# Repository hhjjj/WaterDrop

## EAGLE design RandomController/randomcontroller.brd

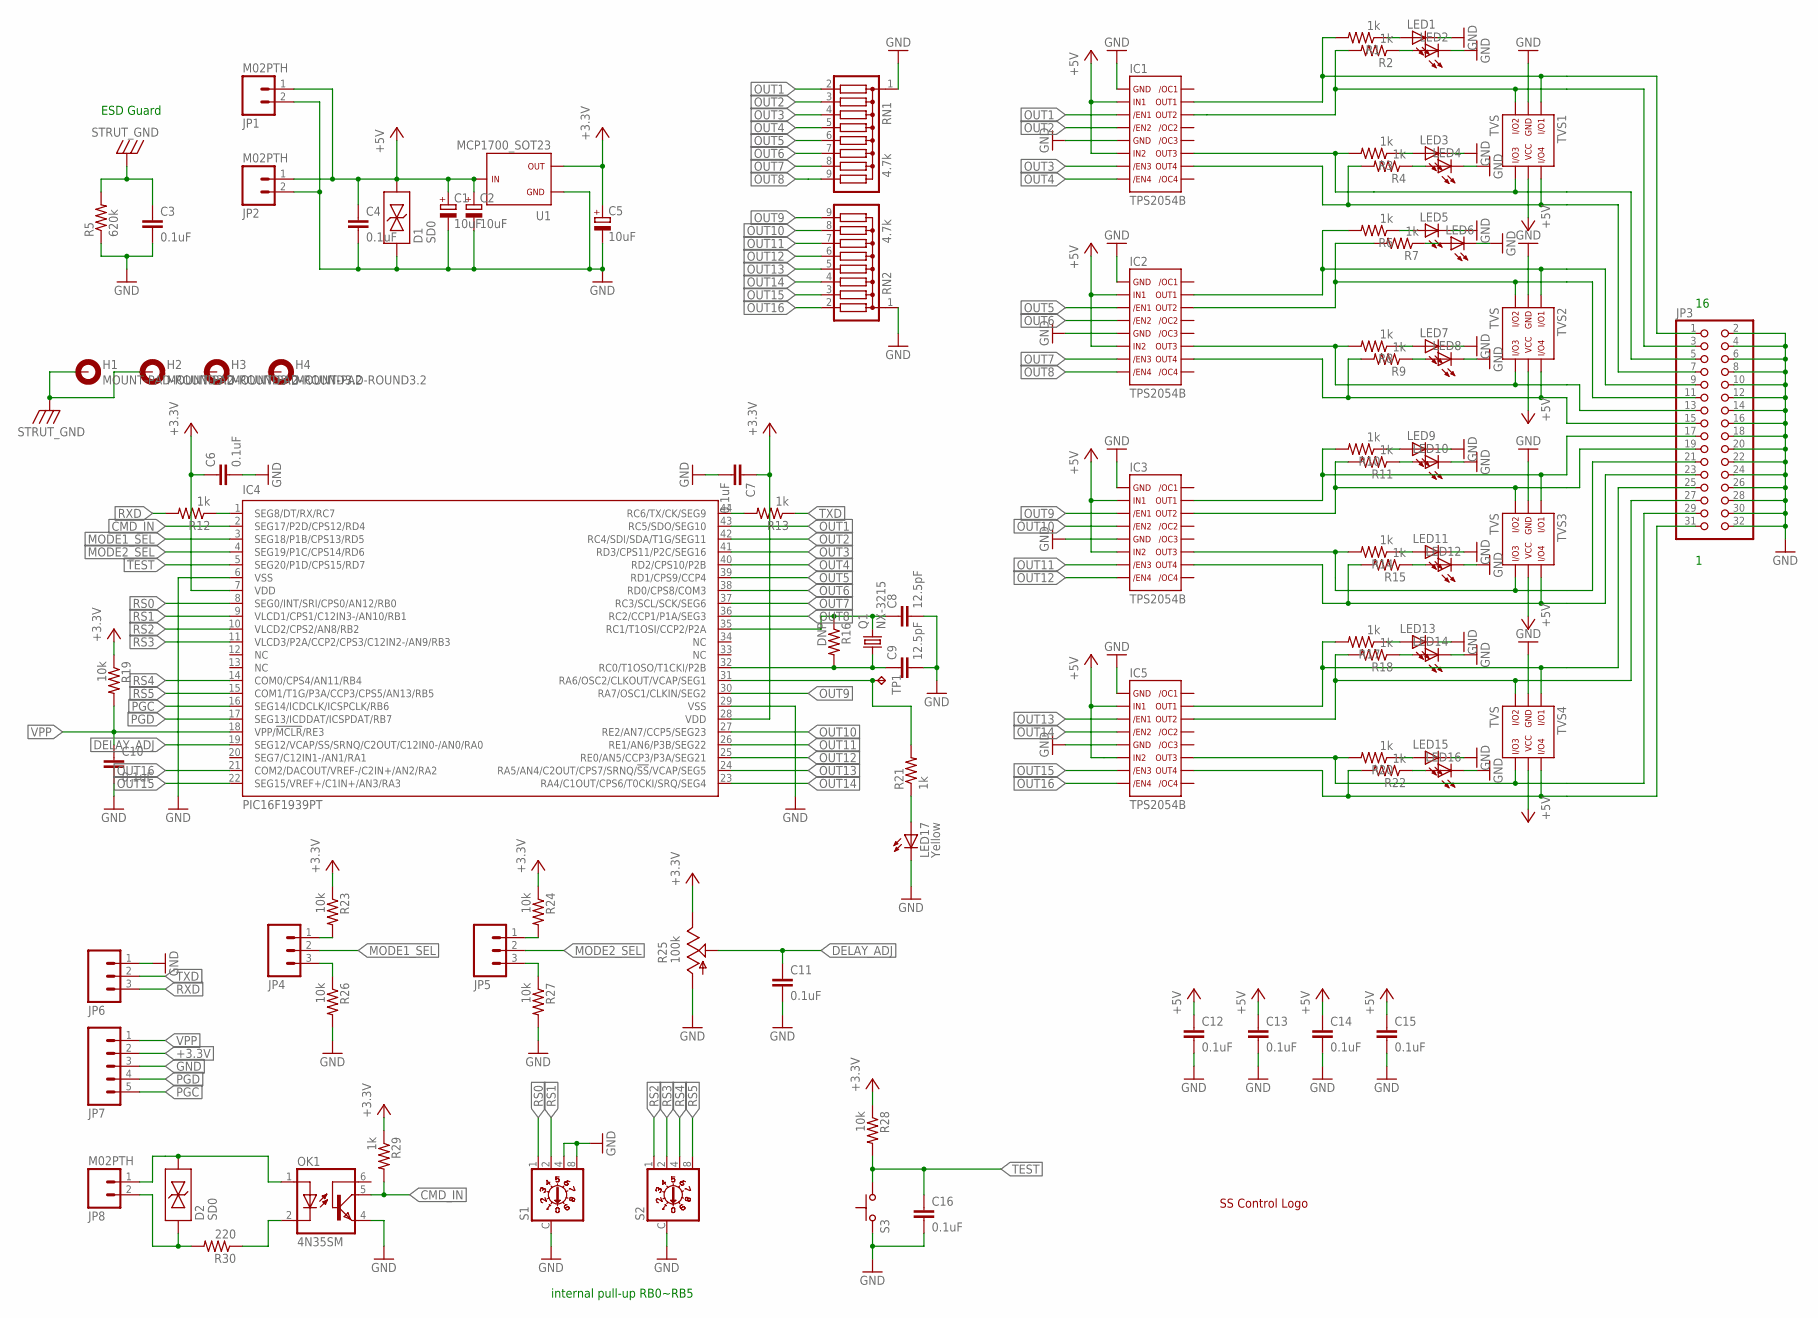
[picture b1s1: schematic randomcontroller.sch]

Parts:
C1, C2, C5: 10uF; C1206(3216)-A
C3, C4, C6, C7, C10, C11, C12, C13, C14, C15, C16: 0.1uF; C0805(2012)
C8, C9: 12.5pF; C0805(2012)
D1, D2: SD0; SOD-323
H1, H2, H3, H4: MOUNT-PAD-ROUND3.2; 3,2-PAD
IC1, IC2, IC3, IC5: TPS2054B; R-PDSO-G16
IC4: PIC16F1939PT; TQFP44
JP1, JP2, JP8: M02PTH; 1X02
JP3: PINHD-2X16/90; 2X16/90
JP4, JP5, JP6: M03PTH; 1X03
JP7: M05PTH; 1X05
LED1, LED2, LED3, LED4, LED5, LED6, LED7, LED8, LED9, LED10, LED11, LED12, LED13, LED14, LED15, LED16: LEDCHIPLED_0805; CHIPLED_0805
LED17: Yellow; CHIPLED_0805
OK1: 4N35SM; DIL6-SMD
Q1: NX-3215
R1, R2, R3, R4, R6, R7, R8, R9, R10, R11, R12, R13, R14, R15, R17, R18, R20, R21, R22, R29: 1k; R0805(2012)
R5: 620k; R0805(2012)
R16: DNP; R0805(2012)
R19, R23, R24, R26, R27, R28: 10k; R0805(2012)
R25: 100k; B25P
R30: 220; R0805(2012)
RN1, RN2: 4.7k; SIL9
S1, S2: S20BCD
S3: SWITCH; SKHLACA010
TP1: TP; TP-13
TVS1, TVS2, TVS3, TVS4: TVS; TSOP-6
U1: MCP1700_SOT23; SOT23
U$1: LOGO; SSCONTROL

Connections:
+3.3V: C5.1 (+), C6.1, C7.1, IC4.7 (VDD), IC4.28 (VDD), JP7.2, R19.1, R23.1, R24.1, R25.E, R28.1, R29.1, U1.2
+5V: C1.1 (+), C2.1 (+), C4.1, C12.1, C13.1, C14.1, C15.1, D1.2, IC1.2, IC1.6, IC2.2, IC2.6, IC3.2, IC3.6, IC5.2, IC5.6, JP1.1, JP2.1, TVS1.5, TVS2.5, TVS3.5, TVS4.5, U1.3
CLKOUT: IC4.31 (RA6/OSC2/CLKOUT/VCAP/SEG1), R21.2, TP1.TP
CMD_IN: IC4.2 (SEG17/P2D/CPS12/RD4), OK1.5 (COL), R29.2
DELAY_ADJ: C11.1, IC4.19 (SEG12/VCAP/SS/SRNQ/C2OUT/C12IN0-/AN0/RA0), R25.S
GND: C1.2 (-), C2.2 (-), C3.2, C4.2, C5.2 (-), C6.2, C7.2, C8.2, C9.2, C10.2, C11.2, C12.2, C13.2, C14.2, C15.2, C16.2, D1.1, IC1.1, IC1.5, IC2.1, IC2.5, IC3.1, IC3.5, IC4.6 (VSS), IC4.29 (VSS), IC5.1, IC5.5, JP1.2, JP2.2, JP3.2, JP3.4, JP3.6, JP3.8, JP3.10, JP3.12, JP3.14, JP3.16, JP3.18, JP3.20, JP3.22, JP3.24, JP3.26, JP3.28, JP3.30, JP3.32, JP6.1, JP7.3, LED1.C, LED2.C, LED3.C, LED4.C, LED5.C, LED6.C, LED7.C, LED8.C, LED9.C, LED10.C, LED11.C, LED12.C, LED13.C, LED14.C, LED15.C, LED16.C, LED17.C, OK1.4 (EMI), R5.1, R25.A, R26.2, R27.2, RN1.1, RN2.1, S1.4, S1.8, S1.C, S2.C, S3.P$1, TVS1.2, TVS2.2, TVS3.2, TVS4.2, U1.1
MODE1_SEL: IC4.3 (SEG18/P1B/CPS13/RD5), JP4.2
MODE2_SEL: IC4.4 (SEG19/P1C/CPS14/RD6), JP5.2
unnamed: D2.2, JP8.1, OK1.1 (A)
unnamed: LED1.A, R1.1
unnamed: OK1.2 (C), R30.1
unnamed: D2.1, JP8.2, R30.2
unnamed: LED2.A, R2.1
unnamed: C8.1, IC4.35 (RC1/T1OSI/CCP2/P2A), Q1.2, R16.1
unnamed: C9.1, IC4.32 (RC0/T1OSO/T1CKI/P2B), Q1.1, R16.2
unnamed: LED3.A, R3.1
unnamed: LED4.A, R4.1
unnamed: LED5.A, R6.1
unnamed: LED6.A, R7.1
unnamed: IC1.15, JP3.1, R1.2, TVS1.1
unnamed: IC1.14, JP3.3, R2.2, TVS1.3
unnamed: IC1.11, JP3.5, R3.2, TVS1.4
unnamed: IC1.10, JP3.7, R4.2, TVS1.6
unnamed: IC2.15, JP3.9, R6.2, TVS2.1
unnamed: IC2.14, JP3.11, R7.2, TVS2.3
unnamed: IC2.11, JP3.13, R8.2, TVS2.4
unnamed: IC2.10, JP3.15, R9.2, TVS2.6
unnamed: IC3.14, JP3.19, R11.2, TVS3.3
unnamed: IC3.11, JP3.21, R14.2, TVS3.4
unnamed: IC3.10, JP3.23, R15.2, TVS3.6
unnamed: IC3.15, JP3.17, R10.2, TVS3.1
unnamed: IC5.14, JP3.27, R18.2, TVS4.3
unnamed: IC5.15, JP3.25, R17.2, TVS4.1
unnamed: IC5.11, JP3.29, R20.2, TVS4.4
unnamed: IC5.10, JP3.31, R22.2, TVS4.6
unnamed: LED9.A, R10.1
unnamed: LED10.A, R11.1
unnamed: LED11.A, R14.1
unnamed: LED12.A, R15.1
unnamed: LED17.A, R21.1
unnamed: LED13.A, R17.1
unnamed: LED14.A, R18.1
unnamed: LED15.A, R20.1
unnamed: LED16.A, R22.1
unnamed: LED7.A, R8.1
unnamed: LED8.A, R9.1
unnamed: IC4.1 (SEG8/DT/RX/RC7), R12.1
unnamed: IC4.44 (RC6/TX/CK/SEG9), R13.2
unnamed: JP5.1, R24.2
unnamed: JP4.1, R23.2
unnamed: JP4.3, R26.1
unnamed: JP5.3, R27.1
OUT1: IC1.3, IC4.43 (RC5/SDO/SEG10), RN1.2
OUT2: IC1.4, IC4.42 (RC4/SDI/SDA/T1G/SEG11), RN1.3
OUT3: IC1.7, IC4.41 (RD3/CPS11/P2C/SEG16), RN1.4
OUT4: IC1.8, IC4.40 (RD2/CPS10/P2B), RN1.5
OUT5: IC2.3, IC4.39 (RD1/CPS9/CCP4), RN1.6
OUT6: IC2.4, IC4.38 (RD0/CPS8/COM3), RN1.7
OUT7: IC2.7, IC4.37 (RC3/SCL/SCK/SEG6), RN1.8
OUT8: IC2.8, IC4.36 (RC2/CCP1/P1A/SEG3), RN1.9
OUT9: IC3.3, IC4.30 (RA7/OSC1/CLKIN/SEG2), RN2.9
OUT10: IC3.4, IC4.27 (RE2/AN7/CCP5/SEG23), RN2.8
OUT11: IC3.7, IC4.26 (RE1/AN6/P3B/SEG22), RN2.7
OUT12: IC3.8, IC4.25 (RE0/AN5/CCP3/P3A/SEG21), RN2.6
OUT13: IC4.24 (RA5/AN4/C2OUT/CPS7/SRNQ/!SS!/VCAP/SEG5), IC5.3, RN2.5
OUT14: IC4.23 (RA4/C1OUT/CPS6/T0CKI/SRQ/SEG4), IC5.4, RN2.4
OUT15: IC4.22 (SEG15/VREF+/C1IN+/AN3/RA3), IC5.7, RN2.3
OUT16: IC4.21 (COM2/DACOUT/VREF-/C2IN+/AN2/RA2), IC5.8, RN2.2
PGC: IC4.16 (SEG14/ICDCLK/ICSPCLK/RB6), JP7.5
PGD: IC4.17 (SEG13/ICDDAT/ICSPDAT/RB7), JP7.4
RS0: IC4.8 (SEG0/INT/SRI/CPS0/AN12/RB0), S1.1
RS1: IC4.9 (VLCD1/CPS1/C12IN3-/AN10/RB1), S1.2
RS2: IC4.10 (VLCD2/CPS2/AN8/RB2), S2.1
RS3: IC4.11 (VLCD3/P2A/CCP2/CPS3/C12IN2-/AN9/RB3), S2.2
RS4: IC4.14 (COM0/CPS4/AN11/RB4), S2.4
RS5: IC4.15 (COM1/T1G/P3A/CCP3/CPS5/AN13/RB5), S2.8
RXD: JP6.3, R12.2
STRUT_GND: C3.1, H1.B3,2, H2.B3,2, R5.2
TEST: C16.1, IC4.5 (SEG20/P1D/CPS15/RD7), R28.2, S3.P$2
TXD: JP6.2, R13.1
VPP: C10.1, IC4.18 (VPP/!MCLR!/RE3), JP7.1, R19.2

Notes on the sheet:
ESD Guard
internal pull-up RB0~RB5

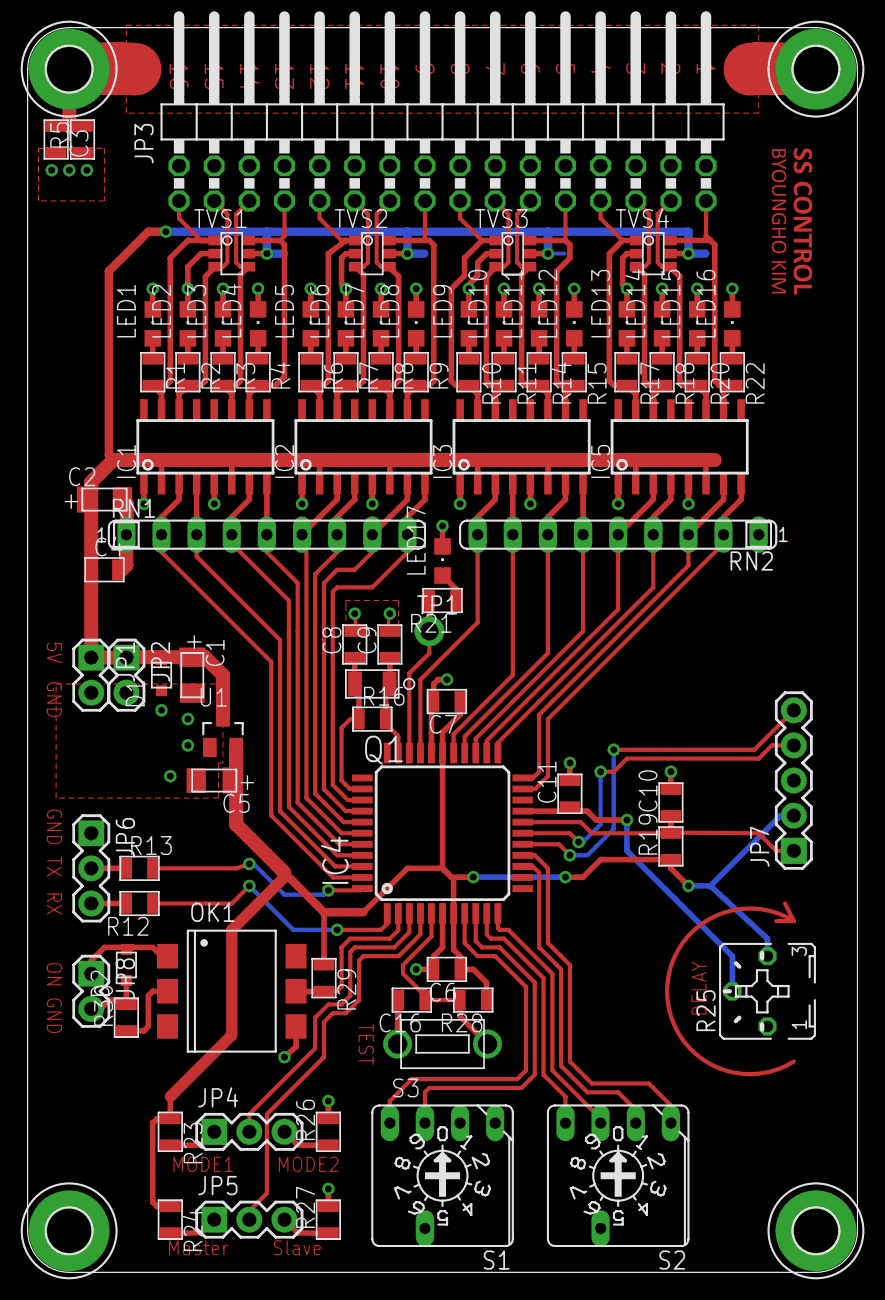
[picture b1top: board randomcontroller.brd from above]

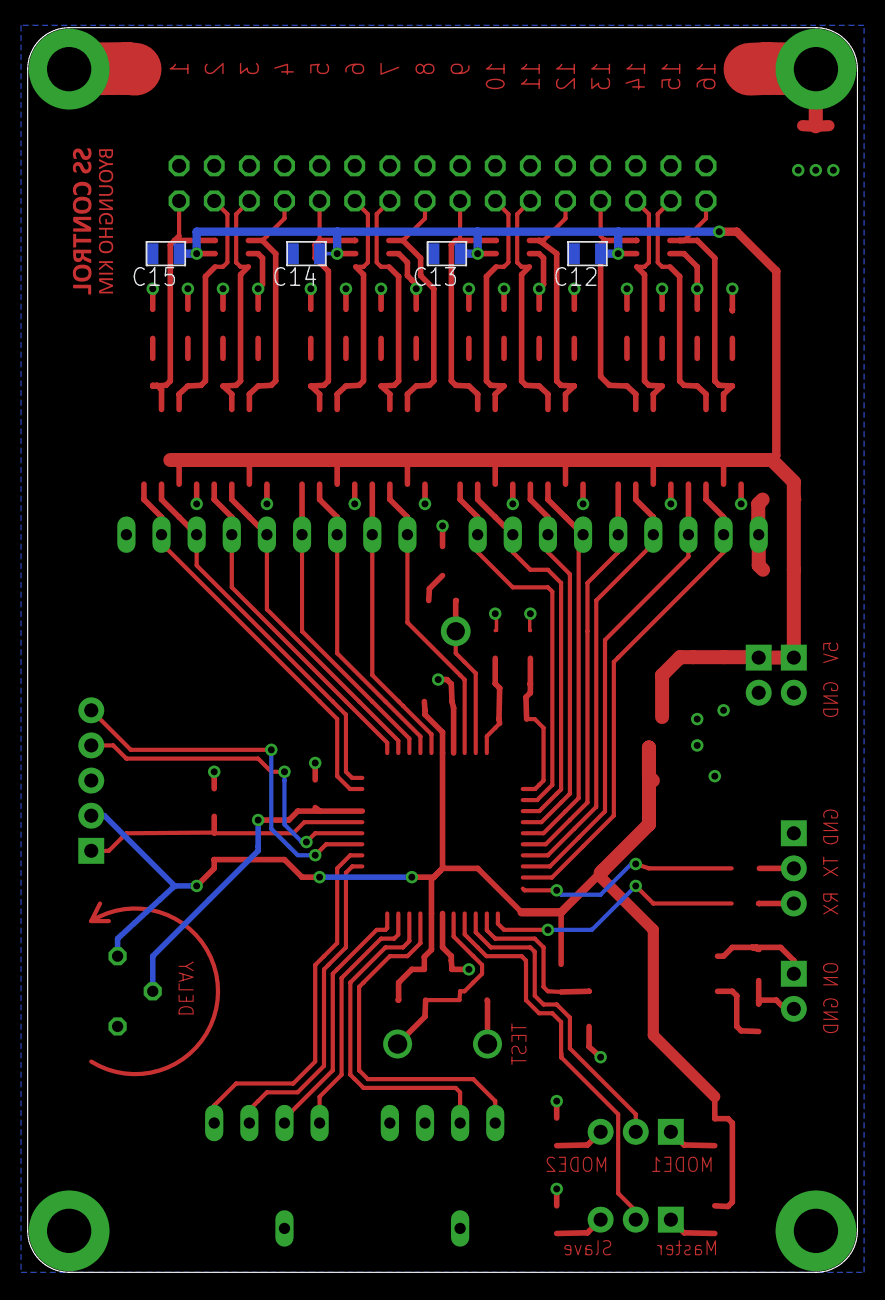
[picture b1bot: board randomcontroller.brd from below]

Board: 2 copper layers, 60.0 x 90.0 mm, 96 parts (4 on the bottom side), 81 nets.

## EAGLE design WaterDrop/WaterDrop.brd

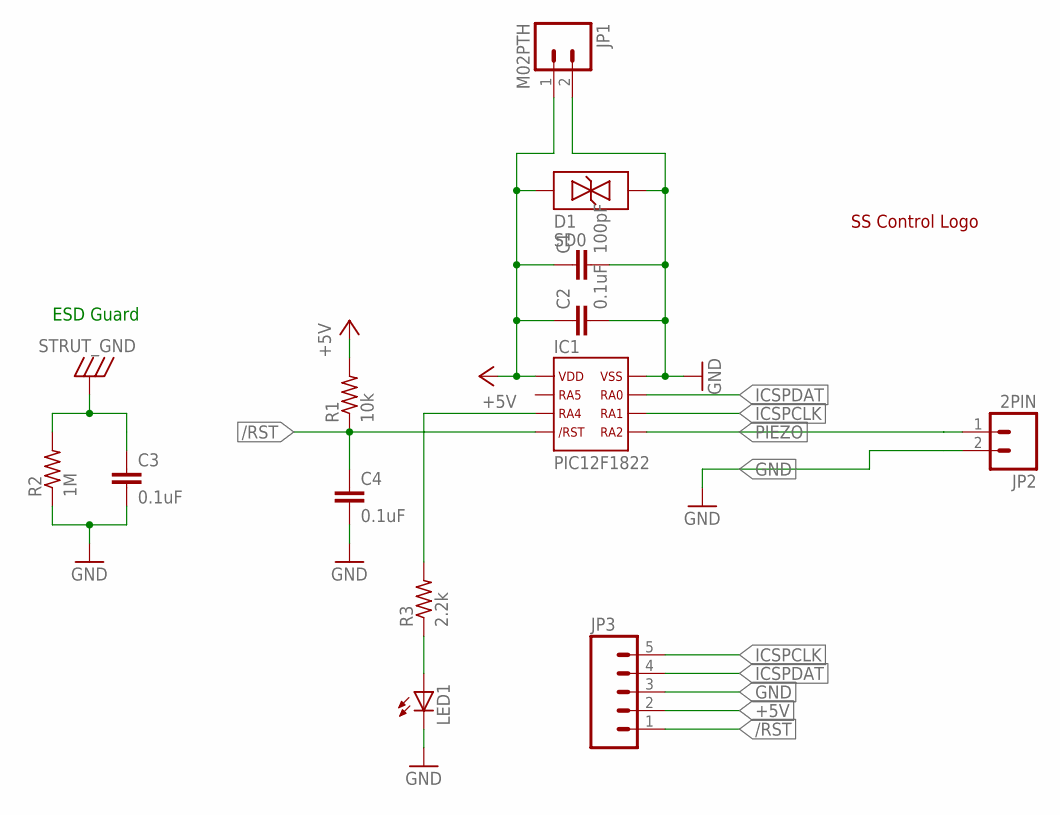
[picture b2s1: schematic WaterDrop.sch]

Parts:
C1: 100pF; C0603(1608)
C2, C3, C4: 0.1uF; C0603(1608)
D1: SD0; SOD-323
IC1: PIC12F1822; SO8
JP1: M02PTH; 1X02
JP2: 2PIN; 2PIN5.08
JP3: M05PTH; 1X05
LED1: LED0603; LED-0603
R1: 10k; R0603(1608)
R2: 1M; R0603(1608)
R3: 2.2k; R0603(1608)
U$1: LOGOPIEZO; SSPIEZOLOGO

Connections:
+5V: C1.1, C2.1, D1.1, IC1.1, JP1.1, JP3.2, R1.2
/RST: C4.1, IC1.4, JP3.1, R1.1
GND: C1.2, C2.2, C3.2, C4.2, D1.2, IC1.8, JP1.2, JP2.2, JP3.3, LED1.C, R2.1
ICSPCLK: IC1.6, JP3.5
ICSPDAT: IC1.7, JP3.4
unnamed: LED1.A, R3.1
unnamed: IC1.3, R3.2
PIEZO: IC1.5, JP2.1
STRUT_GND: C3.1, R2.2

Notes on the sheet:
ESD Guard

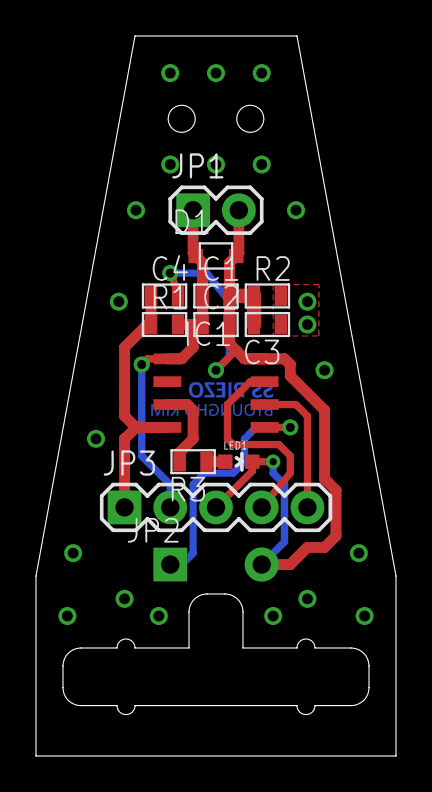
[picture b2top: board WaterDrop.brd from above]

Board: 2 copper layers, 20.0 x 40.0 mm, 14 parts (1 on the bottom side), 9 nets.

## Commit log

2013-06-23 board almost done
2013-07-03 random cotroller added
2013-07-06 random controller first version
2013-07-07 waterdrop and random controller gerber
2013-07-07 all gerber merged
2013-07-10 schmatic renumbered final merged gerber for fab
2013-07-10 part list added

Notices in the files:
parts and their libraries:
SparkFun-Connectors: Licensing: CC v3.0 Share-Alike You are welcome to use this library for commercial purposes.
